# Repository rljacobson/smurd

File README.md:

# The Tardis Keyboard Computer: <br>Project Smurd

For more information about Project Smurd, see [Keyboard Notes.md](./Keyboard%20Notes.md).

## Contents

- Arduino - Microcontroller source code to drive the key matrix scanner.
- Photos - Various photos of the device and its components. 
  - TardisBuilders - Photos of another keyboard of the same model.
- Circuit Reverse Engineering - Identification and wiring of the electronic components
  - Button Matric PCB - The PCB onto which the keys are soldered is completely reverse engineered
  - Logic Board Labelled - Electronic components on the logic board are identified
  - Logic Board Wiring - A mostly complete trace route identification of the logic board
- EEPROM - The contents of the persistent data storage of the device.
  - `Empros 8830-101 (ROM No 56600413 27, Aug 1992), U4 EPROM` - The raw binary dump of the EEPROM
  - `Empros 8830-101 (ROM No 56600413 27, Aug 1992), U4 EPROM.dump` - A "hex dump" of the data
  - KeyboardOS - Artifacts from Ghidra
    - `disassembly.html` - Human-readable disassembly of the Z80 machine code
    - `decompiled_c.html` & `decompiled.c` - Ghidra's decompilation to C.
    - `KeyboardOS.gpr` - Ghidra project file
    - `KeyboardOS.rep` - Ghidra's internal files, not human readable

## Device Information

|                      |                                                              |                                                              |
| -------------------- | ------------------------------------------------------------ | ------------------------------------------------------------ |
| Manufacturer         | Control Data Corporation and and Empros Systems International | "CDC's Energy Management Division was one of its most successful business units, providing control systems solutions that managed as much as 25% of all electricity on the planet. In 1988 or 1989, this division was renamed Empros and was later sold to Siemens as CDC broke apart.[[28\]](https://en.wikipedia.org/wiki/Control_Data_Corporation#cite_note-29)" |
| Manufactured For     | The National Grid Company plc<br>Contract No. FCGCP/-/I1080  | "Intended For..."                                            |
| Name(s)              | Operations Keyboard, Keyboard NGC                            | The same across at least two keyboards.                      |
| Equipment ID NO.     | Multiple: CA312B, QSE 36444                                  | The same across at least two keyboards.                      |
| Part Number          | Multiple: 56598681, 56599470                                 | The same across at least two keyboards. Part numbers found within the device and on the EEPROM have the form 5659XXXX. |
| HPC/EC NO.           | 56598681                                                     | The same across at least two keyboards.                      |
| Series Code          | 01                                                           | The same across at least two keyboards.                      |
| Product Model        | 8830-101                                                     | The same across at least two keyboards.                      |
| Known serial numbers | 1037, 1046                                                   |                                                              |
| Firmware             | ROM PART NUMBER IS 56600413 27 AUG 1992                      | Data embedded in EEPROM.                                     |
| Installation Date    | 24/9/92 for serial numbers 1037 & 1046                       | Installed by A. Williams?                                    |
| Additional ID        | 56598203 E<br/>EM 9146                                       | Small sticker on back, top. The same across at least two keyboards. |

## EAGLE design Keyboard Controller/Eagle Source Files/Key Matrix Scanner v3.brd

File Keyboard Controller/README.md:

# Keyboard Controller

There was always a chance that I wouldn't be able to get the original hardware to work, so from the very beginning I planned on designing a keyboard controller to drive the key matrix PCB and connect it to my computer as a USB HID device, bypassing the original logic board altogether. There are two pieces to the controller: the key matrix scanner and the LED driver.

## Key Matrix Scanner

The key matrix scanner is the brains of the operation. The parallel rows of pins in the back left in the image above is for mounting a "Blue Pill" STM32F103CT6 microcontroller. The only traces connected to those pins are +3V3 and GND. The microcontroller communicates with the board by the 5X2 pin header right at the center of the board. As a consequence of this design, it is trivial to use a different microcontroller with the board. Only 5 of those pins need to connect to the MCU; the other 5 pins are to tap into the lines for debugging or expansion. The 60 pin right angle header connects to the ribbon cable that goes to the key button PCB. Without the LED board attached, the Blue Pill can scan the entire key matrix in ~220 microseconds, or ~4,500 times a second. This is far faster than necessary. What's more, the scanning can be offloaded to the SPI and DMA hardware, freeing the STM32 to do other tasks.

The dual 10X2 pin headers on the right side allow the key matrix scanner board to connect to the LED driver board through a 20 pin ribbon cable. Again, only one of the two 10X2 pin headers is required. The second header is for debugging or expansion. 

Here's the unsoldered custom PCB:

## LED Driver

The LED driver board also has dual 10X2 headers, with the second header just a duplicate of the first. The abundance of unused pins on the 10X2 header leaves plenty of room for further expansion. The LEDs can be driven at ~400 KHz. Brightness can be controlled dynamically by varying the duty cycle (PWM).

## Connectivity

The Blue Pill has a micro USB port and will appear as a USB keyboard. Other setups are possible. For example, an ESP32 would provide Bluetooth and possibly USB as well and would be very power efficient. However, hardware support is farther away for the ESP32.

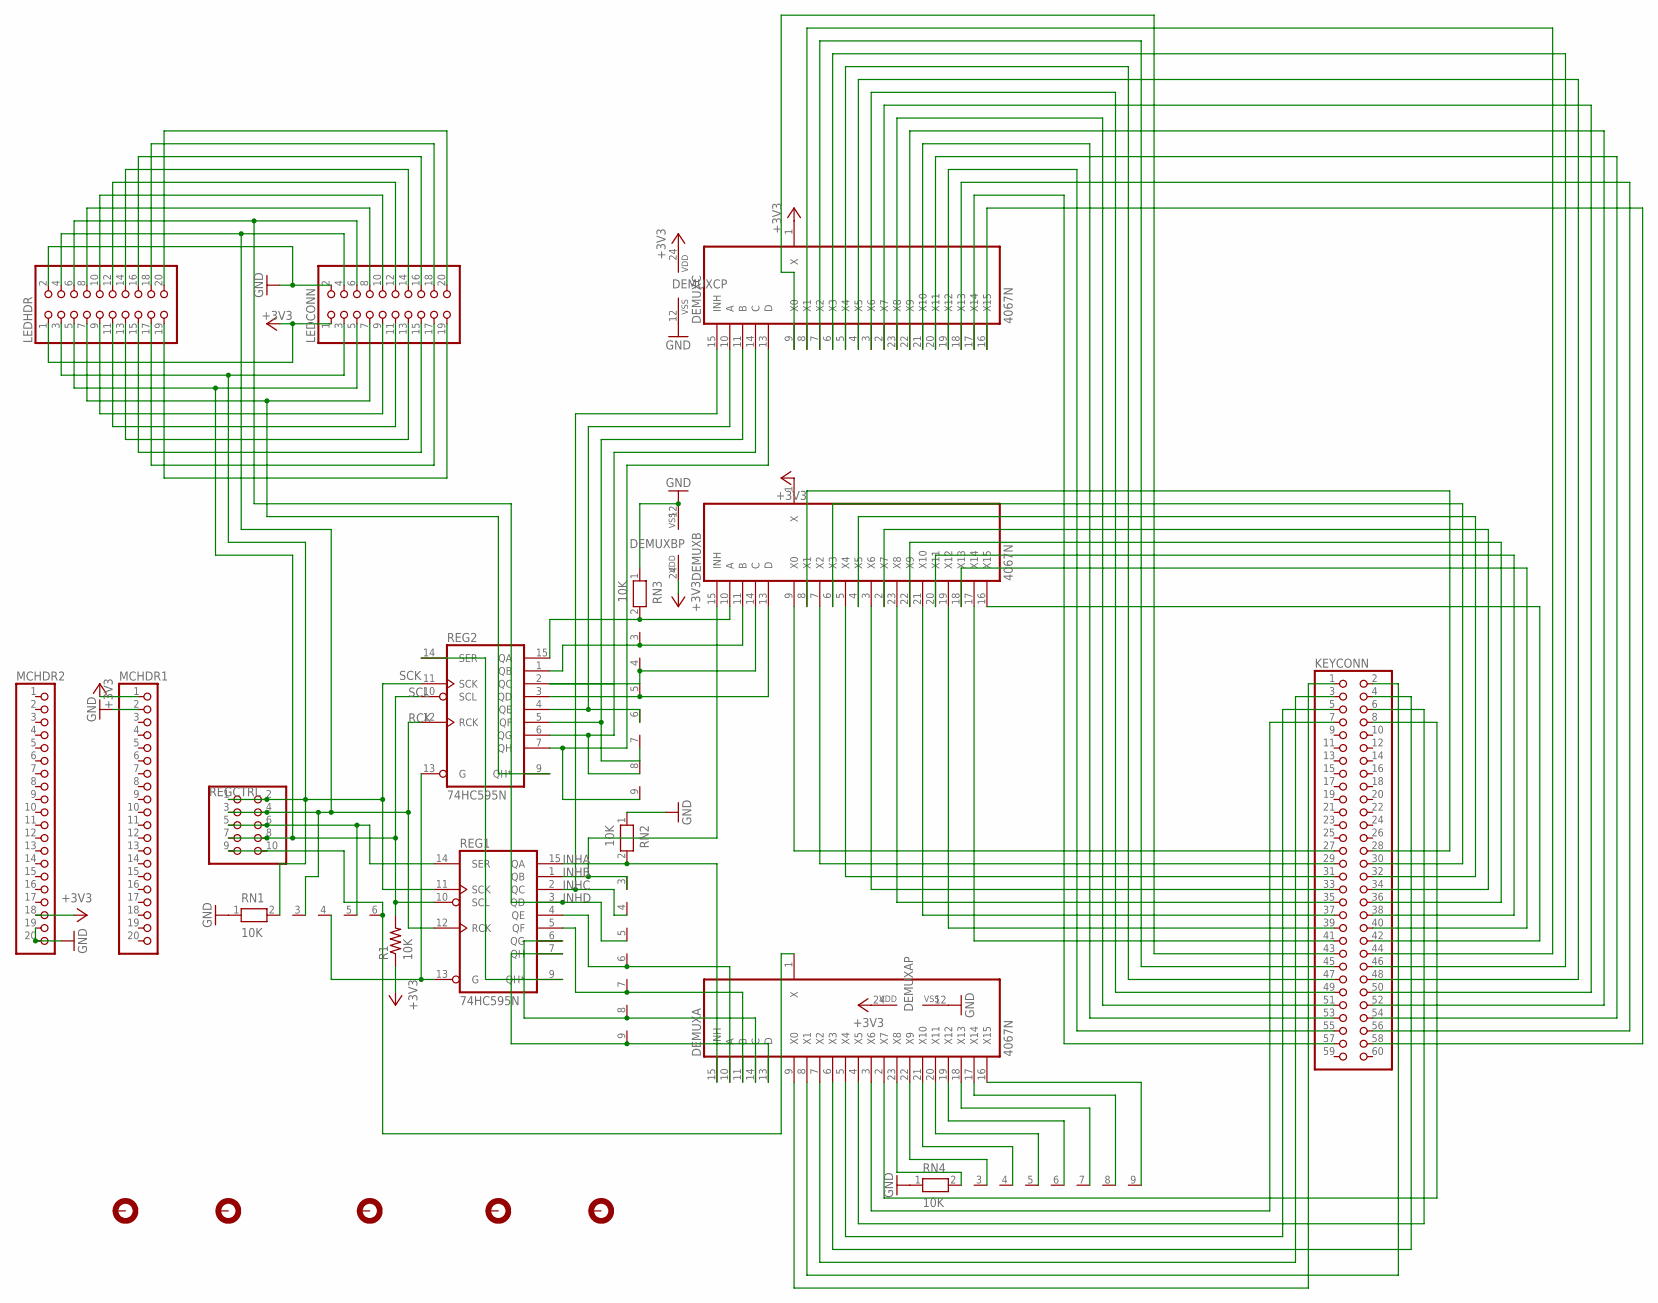
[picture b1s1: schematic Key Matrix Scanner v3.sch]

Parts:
DEMUXA: 4067N; DIL24-6
DEMUXB: 4067N; DIL24-6
DEMUXC: 4067N; DIL24-6
H1, H2, H3, H4, H5: MOUNT-PAD-ROUND3.0; 3,0-PAD
KEYCONN: PINHD-2X30/90; 2X30/90
LEDCONN: PINHD-2X10; 2X10
LEDHDR: PINHD-2X10; 2X10
MCHDR1, MCHDR2: PINHD-1X20; 1X20
R1: 10K; 0204/7
REG1, REG2: 74HC595N; DIL16
REGCTRL: PINHD-2X5; 2X05
RN1: 10K; RN-6
RN2, RN3, RN4: 10K; RN-9

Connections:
+3V3: DEMUXA.24 (VDD), DEMUXB.1 (X), DEMUXB.24 (VDD), DEMUXC.1 (X), DEMUXC.24 (VDD), LEDCONN.1, LEDHDR.1, MCHDR1.1, MCHDR2.18, R1.1, REG1.16 (VCC), REG2.16 (VCC)
DATA: REG1.14 (SER), REGCTRL.5, REGCTRL.6, RN1.5
GND: DEMUXA.12 (VSS), DEMUXB.12 (VSS), DEMUXC.12 (VSS), LEDCONN.2, LEDHDR.2, MCHDR1.2, MCHDR2.19, MCHDR2.20, REG1.8 (GND), REG2.8 (GND), RN1.1, RN2.1, RN3.1, RN4.1
INHA: DEMUXA.15 (INH), REG1.15 (QA), RN2.2
INHB: DEMUXB.15 (INH), REG1.1 (QB), RN2.3
INHC: DEMUXC.15 (INH), REG1.2 (QC), RN2.4
INHD: LEDCONN.6, LEDHDR.6, REG1.3 (QD), RN2.5
KEYREAD: DEMUXA.1 (X), REGCTRL.9, REGCTRL.10, RN1.6
unnamed: DEMUXC.13 (D), REG2.7 (QH), RN3.9
unnamed: DEMUXA.9 (X0), KEYCONN.1
unnamed: REG1.9 (QH*), REG2.14 (SER)
unnamed: LEDCONN.8, LEDHDR.8
unnamed: LEDCONN.10, LEDHDR.10
unnamed: LEDCONN.12, LEDHDR.12
unnamed: LEDCONN.14, LEDHDR.14
unnamed: LEDCONN.16, LEDHDR.16
unnamed: LEDCONN.18, LEDHDR.18
unnamed: LEDCONN.20, LEDHDR.20
unnamed: DEMUXB.22 (X9), KEYCONN.36
unnamed: DEMUXA.8 (X1), KEYCONN.2
unnamed: DEMUXA.7 (X2), KEYCONN.3
unnamed: LEDCONN.9, LEDHDR.9
unnamed: LEDCONN.11, LEDHDR.11
unnamed: LEDCONN.13, LEDHDR.13
unnamed: LEDCONN.15, LEDHDR.15
unnamed: LEDCONN.17, LEDHDR.17
unnamed: LEDCONN.19, LEDHDR.19
unnamed: DEMUXC.14 (C), REG2.6 (QG), RN3.8
unnamed: DEMUXC.11 (B), REG2.5 (QF), RN3.7
unnamed: DEMUXC.10 (A), REG2.4 (QE), RN3.6
unnamed: DEMUXA.6 (X3), KEYCONN.4
unnamed: DEMUXA.13 (D), REG1.7 (QH), RN2.9
unnamed: DEMUXB.14 (C), REG2.2 (QC), RN3.4
unnamed: DEMUXB.11 (B), REG2.1 (QB), RN3.3
unnamed: DEMUXA.22 (X9), RN4.3
unnamed: DEMUXA.5 (X4), KEYCONN.5
unnamed: DEMUXA.10 (A), REG1.4 (QE), RN2.6
unnamed: DEMUXA.21 (X10), RN4.4
unnamed: DEMUXA.20 (X11), RN4.5
unnamed: DEMUXA.4 (X5), KEYCONN.6
unnamed: DEMUXA.3 (X6), KEYCONN.7
unnamed: DEMUXA.2 (X7), KEYCONN.8
unnamed: DEMUXB.9 (X0), KEYCONN.27
unnamed: DEMUXB.8 (X1), KEYCONN.28
unnamed: DEMUXA.19 (X12), RN4.6
unnamed: DEMUXA.18 (X13), RN4.7
unnamed: DEMUXB.13 (D), REG2.3 (QD), RN3.5
unnamed: DEMUXB.10 (A), REG2.15 (QA), RN3.2
unnamed: DEMUXB.7 (X2), KEYCONN.29
unnamed: DEMUXB.6 (X3), KEYCONN.30
unnamed: DEMUXB.5 (X4), KEYCONN.31
unnamed: DEMUXB.4 (X5), KEYCONN.32
unnamed: DEMUXB.3 (X6), KEYCONN.33
unnamed: DEMUXB.2 (X7), KEYCONN.34
unnamed: DEMUXB.23 (X8), KEYCONN.35
unnamed: DEMUXA.14 (C), REG1.6 (QG), RN2.8
unnamed: DEMUXB.21 (X10), KEYCONN.37
unnamed: DEMUXB.20 (X11), KEYCONN.38
unnamed: DEMUXB.19 (X12), KEYCONN.39
unnamed: DEMUXB.18 (X13), KEYCONN.40
unnamed: DEMUXB.17 (X14), KEYCONN.41
unnamed: DEMUXB.16 (X15), KEYCONN.42
unnamed: DEMUXC.9 (X0), KEYCONN.43
unnamed: DEMUXC.8 (X1), KEYCONN.44
unnamed: DEMUXC.7 (X2), KEYCONN.45
unnamed: DEMUXC.6 (X3), KEYCONN.46
unnamed: DEMUXC.5 (X4), KEYCONN.47
unnamed: DEMUXC.4 (X5), KEYCONN.48
unnamed: DEMUXC.3 (X6), KEYCONN.49
unnamed: DEMUXC.2 (X7), KEYCONN.50
unnamed: DEMUXC.23 (X8), KEYCONN.51
unnamed: DEMUXC.22 (X9), KEYCONN.52
unnamed: DEMUXC.20 (X11), KEYCONN.54
unnamed: DEMUXC.21 (X10), KEYCONN.53
unnamed: DEMUXC.19 (X12), KEYCONN.55
unnamed: DEMUXC.18 (X13), KEYCONN.56
unnamed: DEMUXC.17 (X14), KEYCONN.57
unnamed: DEMUXC.16 (X15), KEYCONN.58
unnamed: DEMUXA.17 (X14), RN4.8
unnamed: DEMUXA.16 (X15), RN4.9
unnamed: DEMUXA.11 (B), REG1.5 (QF), RN2.7
unnamed: REG1.13 (G), REG2.13 (G), RN1.4
unnamed: DEMUXA.23 (X8), RN4.2
RCK: LEDCONN.4, LEDHDR.4, REG1.12 (RCK), REG2.12 (RCK), REGCTRL.3, REGCTRL.4, RN1.3
REG3DATA: LEDCONN.7, LEDHDR.7, REG2.9 (QH*)
SCK: LEDCONN.3, LEDHDR.3, REG1.11 (SCK), REG2.11 (SCK), REGCTRL.1, REGCTRL.2, RN1.2
SCL: LEDCONN.5, LEDHDR.5, R1.2, REG1.10 (SCL), REG2.10 (SCL), REGCTRL.7, REGCTRL.8

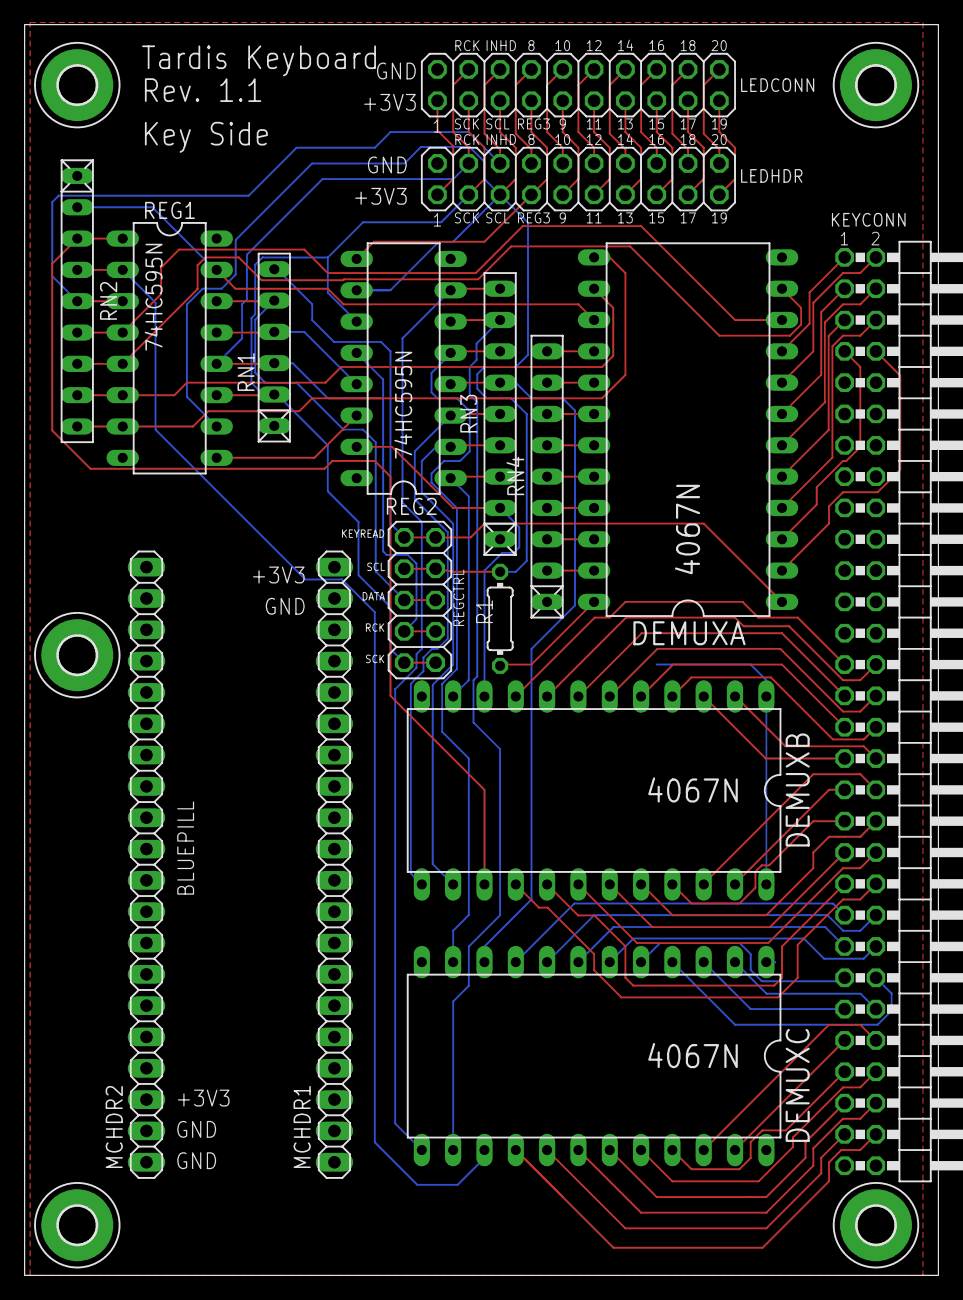
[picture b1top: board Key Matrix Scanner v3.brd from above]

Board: 2 copper layers, 74.1 x 101.4 mm, 21 parts (0 on the bottom side), 87 nets.

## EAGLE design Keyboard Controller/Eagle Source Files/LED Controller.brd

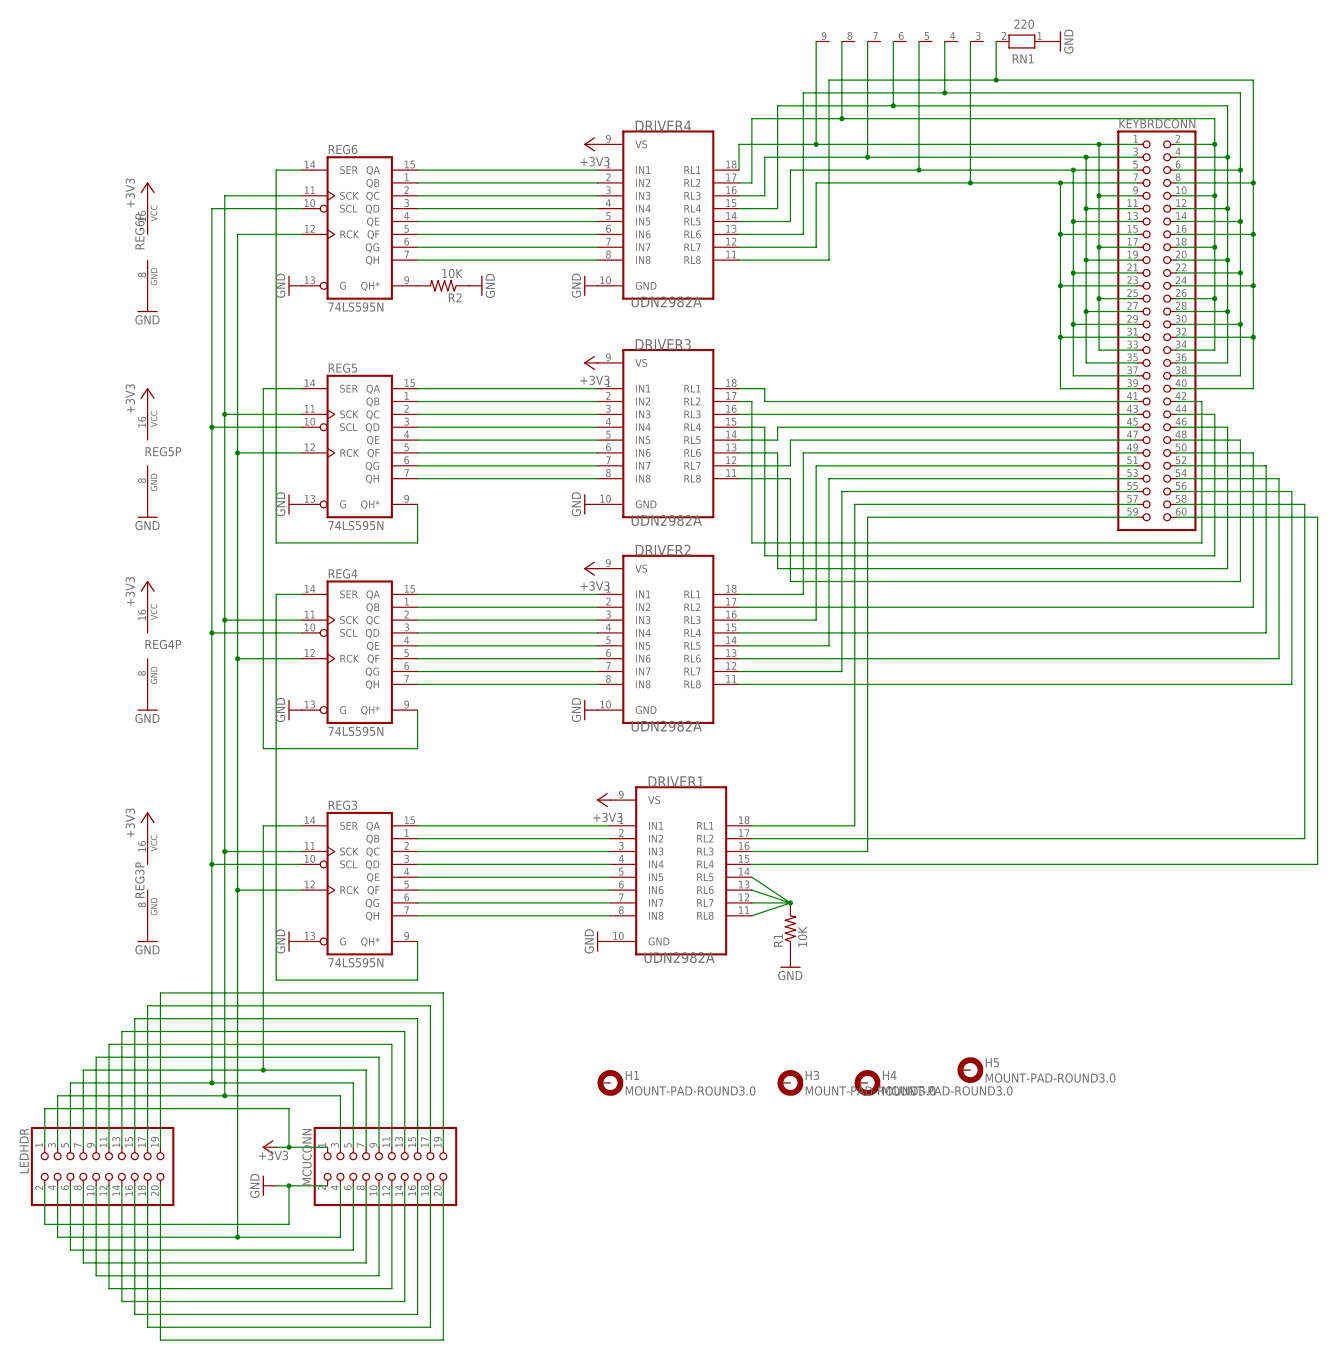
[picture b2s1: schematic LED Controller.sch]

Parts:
DRIVER1, DRIVER2, DRIVER3, DRIVER4: UDN2982A; DIL18
H1, H3, H4, H5: MOUNT-PAD-ROUND3.0; 3,0-PAD
KEYBRDCONN: PINHD-2X30/90; 2X30/90
LEDHDR: PINHD-2X10; 2X10
MCUCONN: PINHD-2X10; 2X10
R1, R2: 10K; VMTA55
REG3, REG4, REG5, REG6: 74LS595N; DIL16
RN1: 220; RN-9

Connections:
+3V3: DRIVER1.9 (VS), DRIVER2.9 (VS), DRIVER3.9 (VS), DRIVER4.9 (VS), LEDHDR.1, MCUCONN.1, REG3.16 (VCC), REG4.16 (VCC), REG5.16 (VCC), REG6.16 (VCC)
GND: DRIVER1.10 (GND), DRIVER2.10 (GND), DRIVER3.10 (GND), DRIVER4.10 (GND), R1.1, R2.1, REG3.8 (GND), REG3.13 (G), REG4.8 (GND), REG4.13 (G), REG5.8 (GND), REG5.13 (G), REG6.8 (GND), REG6.13 (G), RN1.1
INHD: LEDHDR.6, MCUCONN.6
unnamed: DRIVER1.8 (IN8), REG3.7 (QH)
unnamed: DRIVER4.2 (IN2), REG6.1 (QB)
unnamed: DRIVER4.3 (IN3), REG6.2 (QC)
unnamed: LEDHDR.8, MCUCONN.8
unnamed: LEDHDR.10, MCUCONN.10
unnamed: LEDHDR.12, MCUCONN.12
unnamed: LEDHDR.14, MCUCONN.14
unnamed: LEDHDR.16, MCUCONN.16
unnamed: LEDHDR.18, MCUCONN.18
unnamed: LEDHDR.20, MCUCONN.20
unnamed: DRIVER4.4 (IN4), REG6.3 (QD)
unnamed: DRIVER1.1 (IN1), REG3.15 (QA)
unnamed: REG3.9 (QH*), REG4.14 (SER)
unnamed: LEDHDR.9, MCUCONN.9
unnamed: LEDHDR.11, MCUCONN.11
unnamed: LEDHDR.13, MCUCONN.13
unnamed: LEDHDR.15, MCUCONN.15
unnamed: LEDHDR.17, MCUCONN.17
unnamed: LEDHDR.19, MCUCONN.19
unnamed: DRIVER4.11 (RL8), KEYBRDCONN.8, KEYBRDCONN.16, KEYBRDCONN.24, KEYBRDCONN.32, KEYBRDCONN.40, RN1.2
unnamed: DRIVER4.13 (RL6), KEYBRDCONN.6, KEYBRDCONN.14, KEYBRDCONN.22, KEYBRDCONN.30, KEYBRDCONN.38, RN1.4
unnamed: DRIVER4.15 (RL4), KEYBRDCONN.4, KEYBRDCONN.12, KEYBRDCONN.20, KEYBRDCONN.28, KEYBRDCONN.36, RN1.6
unnamed: DRIVER4.17 (RL2), KEYBRDCONN.2, KEYBRDCONN.10, KEYBRDCONN.18, KEYBRDCONN.26, KEYBRDCONN.34, RN1.8
unnamed: DRIVER1.2 (IN2), REG3.1 (QB)
unnamed: DRIVER4.18 (RL1), KEYBRDCONN.1, KEYBRDCONN.9, KEYBRDCONN.17, KEYBRDCONN.25, KEYBRDCONN.33, RN1.9
unnamed: DRIVER1.3 (IN3), REG3.2 (QC)
unnamed: DRIVER4.5 (IN5), REG6.4 (QE)
unnamed: DRIVER4.6 (IN6), REG6.5 (QF)
unnamed: DRIVER4.7 (IN7), REG6.6 (QG)
unnamed: DRIVER1.4 (IN4), REG3.3 (QD)
unnamed: DRIVER4.16 (RL3), KEYBRDCONN.3, KEYBRDCONN.11, KEYBRDCONN.19, KEYBRDCONN.27, KEYBRDCONN.35, RN1.7
unnamed: DRIVER4.14 (RL5), KEYBRDCONN.5, KEYBRDCONN.13, KEYBRDCONN.21, KEYBRDCONN.29, KEYBRDCONN.37, RN1.5
unnamed: DRIVER4.12 (RL7), KEYBRDCONN.7, KEYBRDCONN.15, KEYBRDCONN.23, KEYBRDCONN.31, KEYBRDCONN.39, RN1.3
unnamed: DRIVER1.5 (IN5), REG3.4 (QE)
unnamed: DRIVER1.6 (IN6), REG3.5 (QF)
unnamed: DRIVER1.7 (IN7), REG3.6 (QG)
unnamed: REG4.9 (QH*), REG5.14 (SER)
unnamed: REG5.9 (QH*), REG6.14 (SER)
unnamed: DRIVER4.8 (IN8), REG6.7 (QH)
unnamed: DRIVER4.1 (IN1), REG6.15 (QA)
unnamed: R2.2, REG6.9 (QH*)
unnamed: DRIVER2.1 (IN1), REG4.15 (QA)
unnamed: DRIVER2.2 (IN2), REG4.1 (QB)
unnamed: DRIVER2.3 (IN3), REG4.2 (QC)
unnamed: DRIVER2.4 (IN4), REG4.3 (QD)
unnamed: DRIVER2.5 (IN5), REG4.4 (QE)
unnamed: DRIVER2.6 (IN6), REG4.5 (QF)
unnamed: DRIVER2.7 (IN7), REG4.6 (QG)
unnamed: DRIVER2.8 (IN8), REG4.7 (QH)
unnamed: DRIVER3.1 (IN1), REG5.15 (QA)
unnamed: DRIVER3.2 (IN2), REG5.1 (QB)
unnamed: DRIVER3.3 (IN3), REG5.2 (QC)
unnamed: DRIVER3.4 (IN4), REG5.3 (QD)
unnamed: DRIVER3.5 (IN5), REG5.4 (QE)
unnamed: DRIVER3.6 (IN6), REG5.5 (QF)
unnamed: DRIVER3.7 (IN7), REG5.6 (QG)
unnamed: DRIVER3.8 (IN8), REG5.7 (QH)
unnamed: DRIVER3.18 (RL1), KEYBRDCONN.41
unnamed: DRIVER3.16 (RL3), KEYBRDCONN.43
unnamed: DRIVER3.14 (RL5), KEYBRDCONN.45
unnamed: DRIVER3.12 (RL7), KEYBRDCONN.47
unnamed: DRIVER3.17 (RL2), KEYBRDCONN.42
unnamed: DRIVER3.15 (RL4), KEYBRDCONN.44
unnamed: DRIVER3.13 (RL6), KEYBRDCONN.46
unnamed: DRIVER3.11 (RL8), KEYBRDCONN.48
unnamed: DRIVER2.18 (RL1), KEYBRDCONN.49
unnamed: DRIVER2.16 (RL3), KEYBRDCONN.51
unnamed: DRIVER2.14 (RL5), KEYBRDCONN.53
unnamed: DRIVER1.18 (RL1), KEYBRDCONN.57
unnamed: DRIVER2.12 (RL7), KEYBRDCONN.55
unnamed: DRIVER2.17 (RL2), KEYBRDCONN.50
unnamed: DRIVER2.15 (RL4), KEYBRDCONN.52
unnamed: DRIVER2.13 (RL6), KEYBRDCONN.54
unnamed: DRIVER2.11 (RL8), KEYBRDCONN.56
unnamed: DRIVER1.16 (RL3), KEYBRDCONN.59
unnamed: DRIVER1.17 (RL2), KEYBRDCONN.58
unnamed: DRIVER1.15 (RL4), KEYBRDCONN.60
unnamed: DRIVER1.11 (RL8), DRIVER1.12 (RL7), DRIVER1.13 (RL6), DRIVER1.14 (RL5), R1.2
RCK: LEDHDR.4, MCUCONN.4, REG3.12 (RCK), REG4.12 (RCK), REG5.12 (RCK), REG6.12 (RCK)
REG3: LEDHDR.2, MCUCONN.2
REG3DATA: LEDHDR.7, MCUCONN.7, REG3.14 (SER)
SCK: LEDHDR.3, MCUCONN.3, REG3.11 (SCK), REG4.11 (SCK), REG5.11 (SCK), REG6.11 (SCK)
SCL: LEDHDR.5, MCUCONN.5, REG3.10 (SCL), REG4.10 (SCL), REG5.10 (SCL), REG6.10 (SCL)

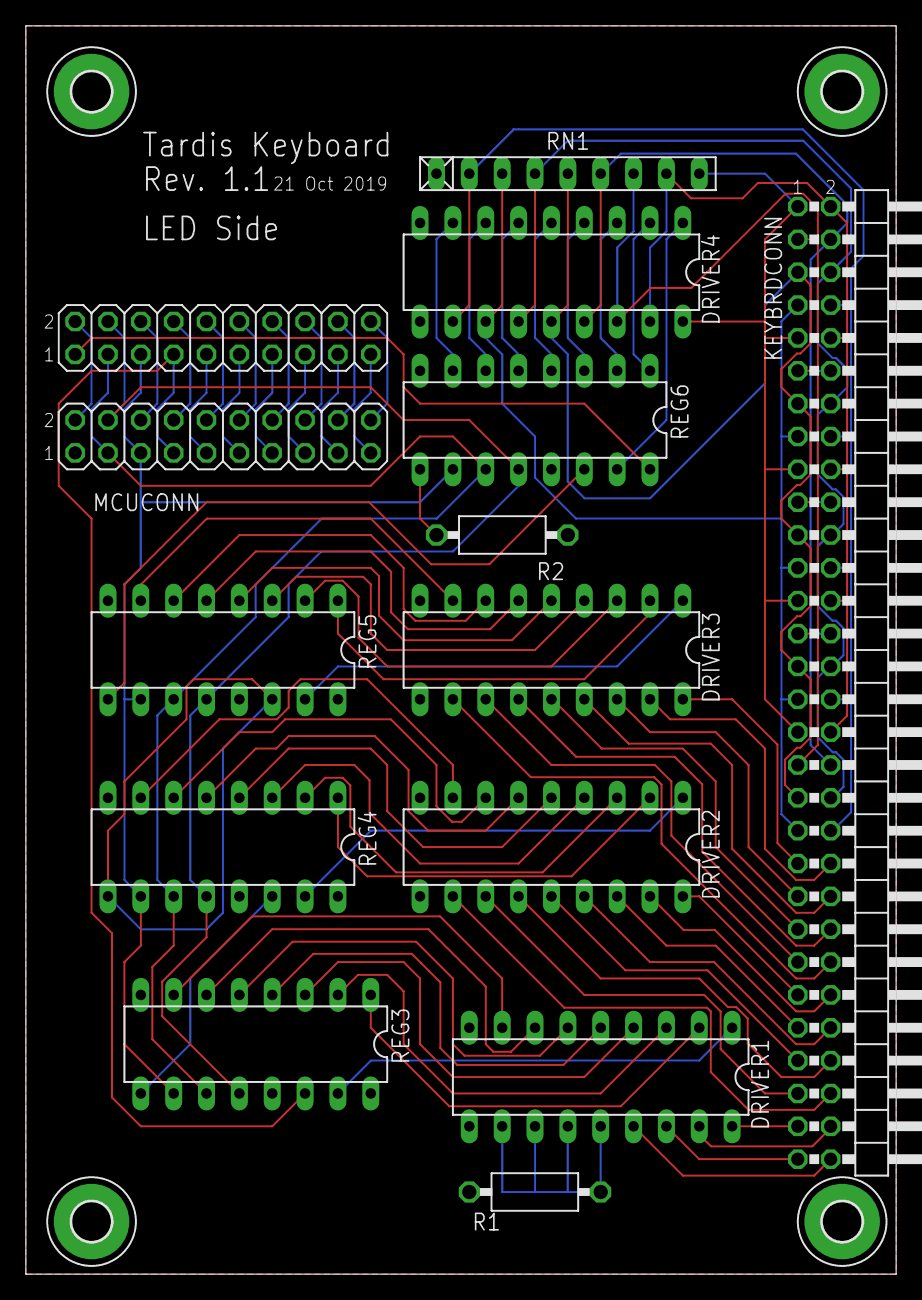
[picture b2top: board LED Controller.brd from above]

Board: 2 copper layers, 67.3 x 96.5 mm, 18 parts (0 on the bottom side), 86 nets.

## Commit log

2019-10-09 Fixed relative links for GFM.
2019-10-09 Fixed image links for GFM.
2019-10-09 Edited some photos, changed permissions.
2019-10-09 Changed photo to cropped version.
2019-10-09 Typo in image url.
2019-10-20 Changed "possible" keys to "addressable," which is clearer.
2019-10-20 Added the word computer.
2019-10-21 Added keyboard controller hardware Gerber files, Eagle sources, etc.
